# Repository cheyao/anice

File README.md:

# Icedev & Anice

*"FPGAs work like this. You don't tell them what to do, you tell them what to BE."*

An FPGA is a chip that can be configured on the hardware level. You can basically make your own CPU and GPU on it.

This project is composed of a PCB duo, that will be later joined together:

The first PCB called "icedev" is a ICE40 FPGA development board:
- 16MHz clock
- 64KiB eeprom
- 128MiB flash
- 1.2MiB of RAM
- dual usb-c
- multi voltage
It's equivalent is like the raspberry pico (orph pico)

The second, called "anice":
- 256MiB of ram
- 128MiB of flash
- HDMI port
- triple USB C with JTAG converter
- SDCard Reader
- dual 25MHz clock and 200MHz built-in clock
- multiple indicator lights
- only 4 layer PCB

View online demo on [kicanvas](https://kicanvas.org/?github=https%3A%2F%2Fgithub.com%2Fcheyao%2Fanice%2Ftree%2Fmain%2Fsrc%2F)!

The repo stucture is a bit messy because I wanted the two designs to appear together on kicanvas.

## Anice:

## Icedev:

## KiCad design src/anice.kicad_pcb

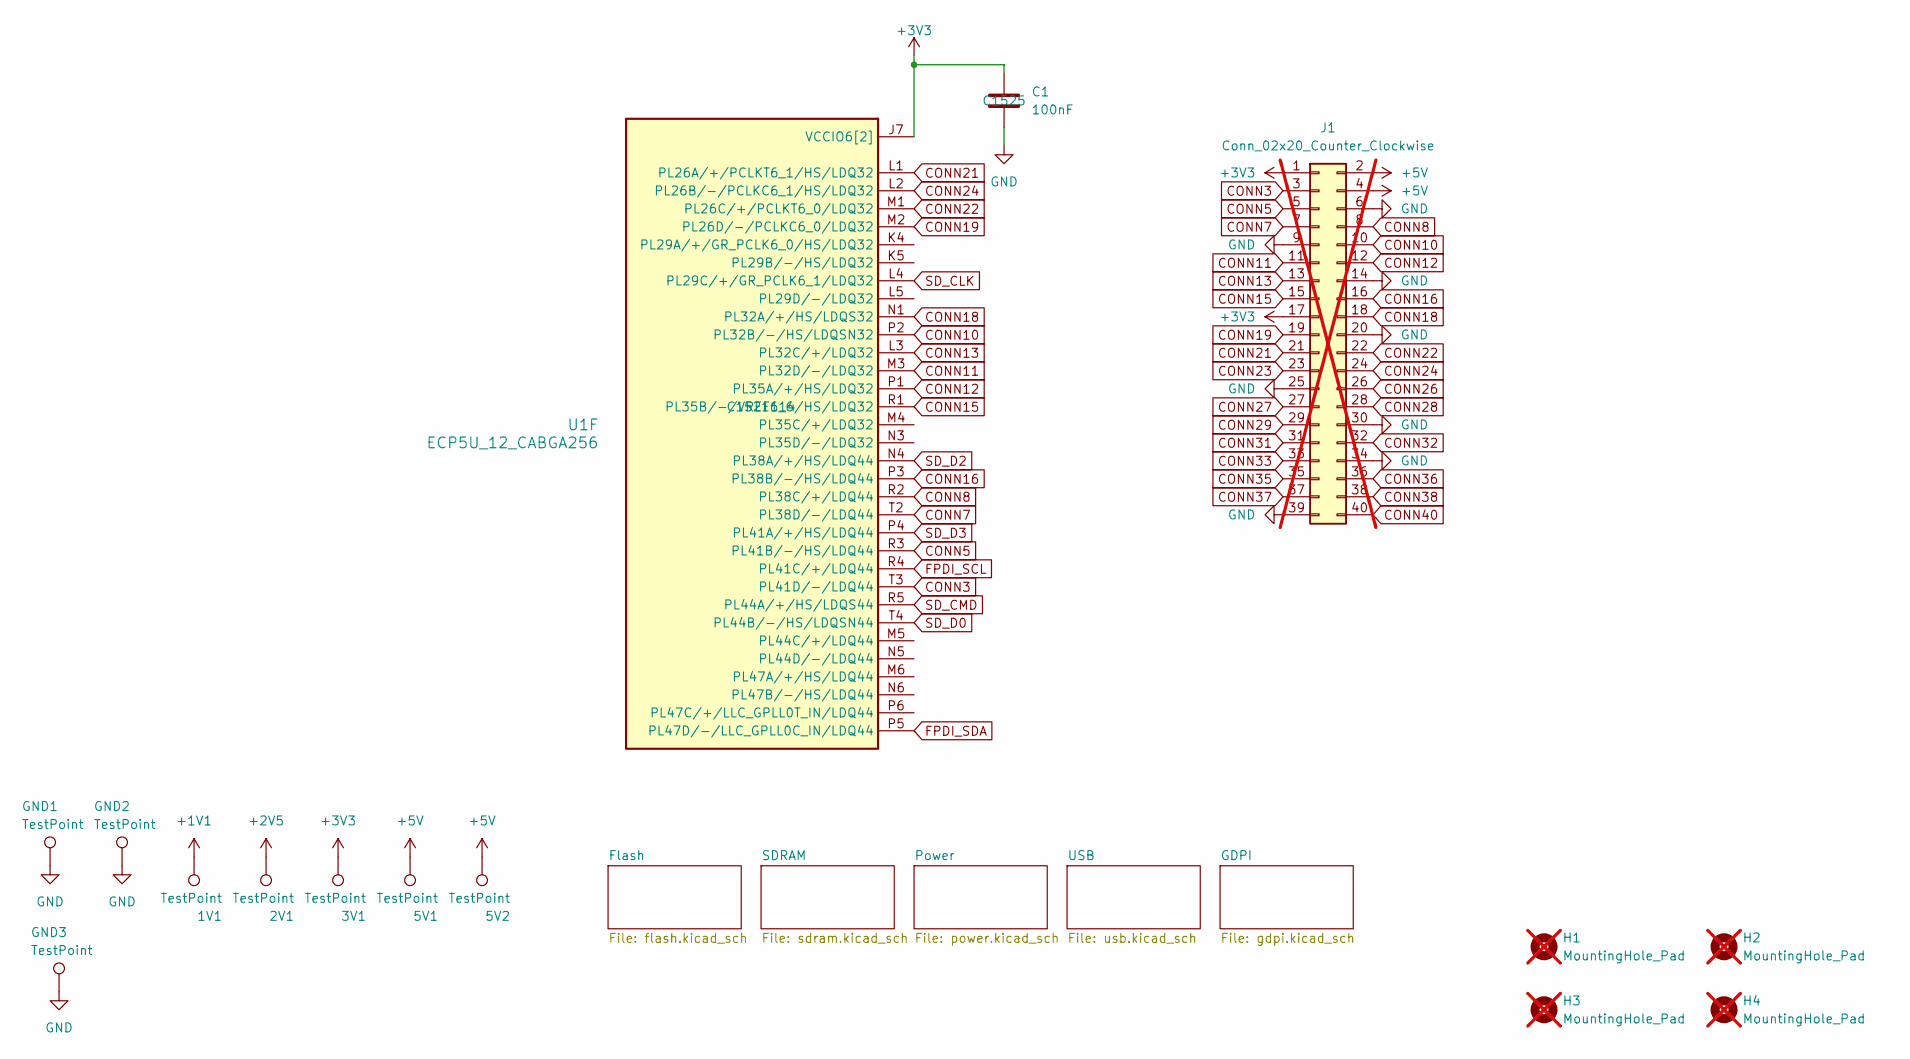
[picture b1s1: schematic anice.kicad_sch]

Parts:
1V1, 2V1, 3V1, 5V1, 5V2: TestPoint; TestPoint_Pad_D1.5mm
C1: 100nF; C_0402_1005Metric; JLCPCB Part # C1525
GND1, GND2, GND3: TestPoint; TestPoint_Pad_D1.5mm
H1, H2, H3, H4: MountingHole_Pad; MountingHole_2.5mm; not fitted
J1: Conn_02x20_Counter_Clockwise; PinHeader_2x20_P2.54mm_Vertical; not fitted
U1: ECP5U_12_CABGA256; BGA-256_14.0x14.0mm_Layout16x16_P0.8mm_Ball0.45mm_Pad0.32mm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; JLCPCB Part # C1521614

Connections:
+1V1: 1V1.1; also elsewhere on the board
+2V5: 2V1.1; also elsewhere on the board
+3V3: 3V1.1, C1.1, J1.1, J1.17, U1.J6 (VCCIO6[2]), U1.J7 (VCCIO6[2]); also elsewhere on the board
+5V: 5V1.1, 5V2.1, J1.2, J1.4; also elsewhere on the board
CONN3: J1.3, U1.T3 (PL41D/-/LDQ44)
CONN5: J1.5, U1.R3 (PL41B/-/HS/LDQ44)
CONN7: J1.7, U1.T2 (PL38D/-/LDQ44)
CONN8: J1.8, U1.R2 (PL38C/+/LDQ44)
CONN10: J1.10, U1.P2 (PL32B/-/HS/LDQSN32)
CONN11: J1.11, U1.M3 (PL32D/-/LDQ32)
CONN12: J1.12, U1.P1 (PL35A/+/HS/LDQ32)
CONN13: J1.13, U1.L3 (PL32C/+/LDQ32)
CONN15: J1.15, U1.R1 (PL35B/-/VREF1_6/HS/LDQ32)
CONN16: J1.16, U1.P3 (PL38B/-/HS/LDQ44)
CONN18: J1.18, U1.N1 (PL32A/+/HS/LDQS32)
CONN19: J1.19, U1.M2 (PL26D/-/PCLKC6_0/LDQ32)
CONN21: J1.21, U1.L1 (PL26A/+/PCLKT6_1/HS/LDQ32)
CONN22: J1.22, U1.M1 (PL26C/+/PCLKT6_0/LDQ32)
CONN23: J1.23; also elsewhere on the board
CONN24: J1.24, U1.L2 (PL26B/-/PCLKC6_1/HS/LDQ32)
CONN26: J1.26; also elsewhere on the board
CONN27: J1.27; also elsewhere on the board
CONN28: J1.28; also elsewhere on the board
CONN29: J1.29; also elsewhere on the board
CONN31: J1.31; also elsewhere on the board
CONN32: J1.32; also elsewhere on the board
CONN33: J1.33; also elsewhere on the board
CONN35: J1.35; also elsewhere on the board
CONN36: J1.36; also elsewhere on the board
CONN37: J1.37; also elsewhere on the board
CONN38: J1.38; also elsewhere on the board
CONN40: J1.40; also elsewhere on the board
FPDI_SCL: U1.R4 (PL41C/+/LDQ44); also elsewhere on the board
FPDI_SDA: U1.P5 (PL47D/-/LLC_GPLL0C_IN/LDQ44); also elsewhere on the board
GND: C1.2, GND1.1, GND2.1, GND3.1, J1.6, J1.9, J1.14, J1.20, J1.25, J1.30, J1.34, J1.39; also elsewhere on the board
SD_CLK: U1.L4 (PL29C/+/GR_PCLK6_1/LDQ32); also elsewhere on the board
SD_CMD: U1.R5 (PL44A/+/HS/LDQS44); also elsewhere on the board
SD_D0: U1.T4 (PL44B/-/HS/LDQSN44); also elsewhere on the board
SD_D2: U1.N4 (PL38A/+/HS/LDQ44); also elsewhere on the board
SD_D3: U1.P4 (PL41A/+/HS/LDQ44); also elsewhere on the board

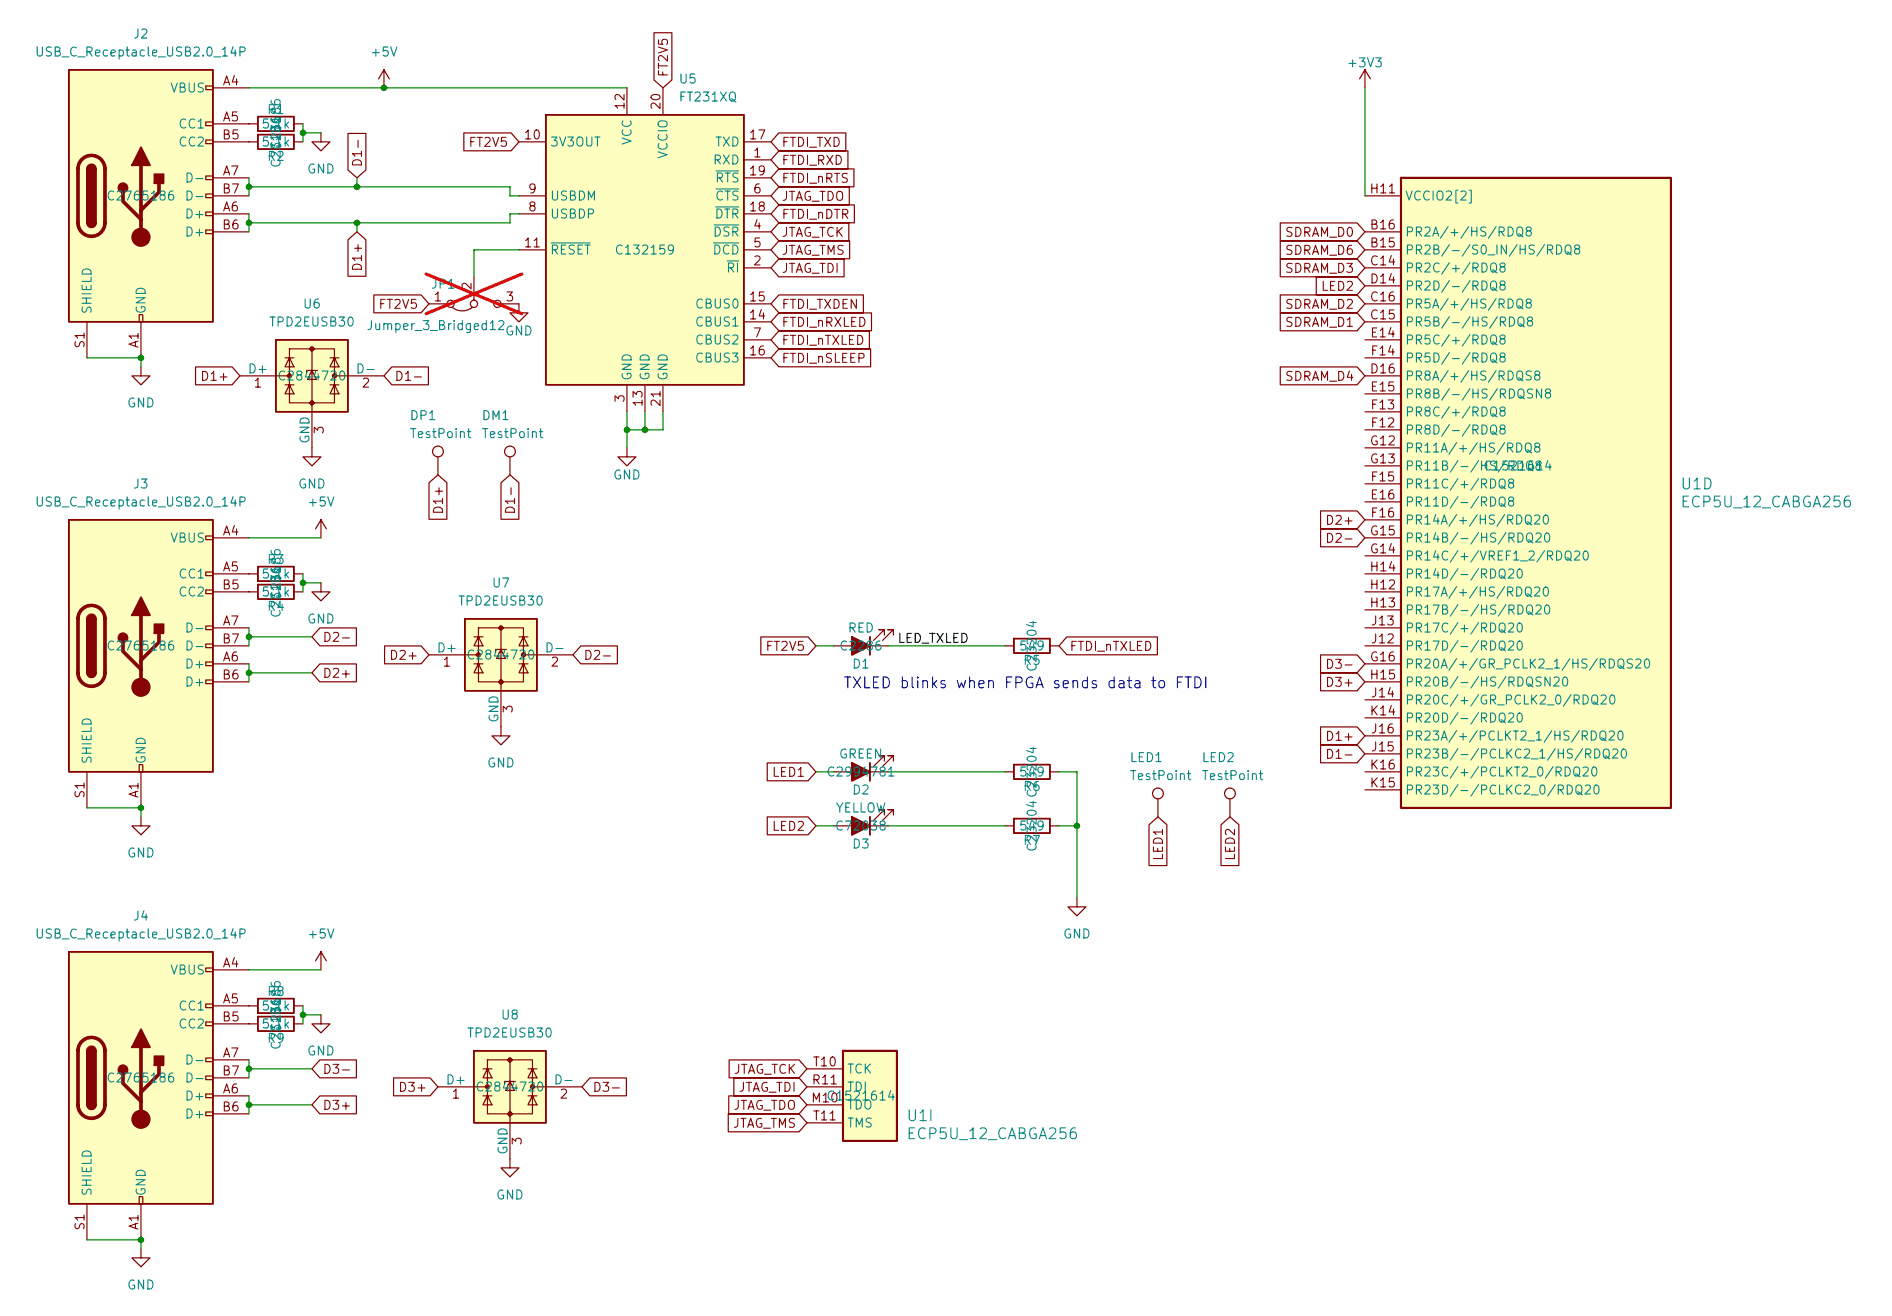
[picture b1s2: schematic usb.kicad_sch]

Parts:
D1: RED; LED_0603_1608Metric; JLCPCB Part # C2286
D2: GREEN; LED_0603_1608Metric; JLCPCB Part # C2994781
D3: YELLOW; LED_0603_1608Metric; JLCPCB Part # C72038
DM1: TestPoint; TestPoint_Pad_D1.5mm
DP1: TestPoint; TestPoint_Pad_D1.5mm
J2, J3, J4: USB_C_Receptacle_USB2.0_14P; USB_C_Receptacle_GCT_USB4105-xx-A_16P_TopMnt_Horizontal; JLCPCB Part # C2765186
JP1: Jumper_3_Bridged12; SolderJumper-3_P1.3mm_Bridged2Bar12_RoundedPad1.0x1.5mm; not fitted
LED1, LED2: TestPoint; TestPoint_Pad_D1.5mm
R1, R2, R3, R4, R8, R9: 5.1k; R_0603_1608Metric; JLCPCB Part # C23186
R5, R6, R7: 549; R_0603_1608Metric; JLCPCB Part # C23204
U1: ECP5U_12_CABGA256; BGA-256_14.0x14.0mm_Layout16x16_P0.8mm_Ball0.45mm_Pad0.32mm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; JLCPCB Part # C1521614
U5: FT231XQ; QFN-20-1EP_4x4mm_P0.5mm_EP2.5x2.5mm; JLCPCB Part # C132159
U6, U7, U8: TPD2EUSB30; Texas_DRT-3; JLCPCB Part # C2844720

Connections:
+3V3: U1.H11 (VCCIO2[2]), U1.J11 (VCCIO2[2]); also elsewhere on the board
+5V: J2.A4 (VBUS), J2.A9 (VBUS), J2.B4 (VBUS), J2.B9 (VBUS), J3.A4 (VBUS), J3.A9 (VBUS), J3.B4 (VBUS), J3.B9 (VBUS), J4.A4 (VBUS), J4.A9 (VBUS), J4.B4 (VBUS), J4.B9 (VBUS), U5.12 (VCC); also elsewhere on the board
/USB/LED_TXLED: D1.1 (K), R5.2
D1+: DP1.1, J2.A6 (D+), J2.B6 (D+), U1.J16 (PR23A/+/PCLKT2_1/HS/RDQ20), U5.8 (USBDP), U6.1 (D+)
D1-: DM1.1, J2.A7 (D-), J2.B7 (D-), U1.J15 (PR23B/-/PCLKC2_1/HS/RDQ20), U5.9 (USBDM), U6.2 (D-)
D2+: J3.A6 (D+), J3.B6 (D+), U1.F16 (PR14A/+/HS/RDQ20), U7.1 (D+)
D2-: J3.A7 (D-), J3.B7 (D-), U1.G15 (PR14B/-/HS/RDQ20), U7.2 (D-)
D3+: J4.A6 (D+), J4.B6 (D+), U1.H15 (PR20B/-/HS/RDQSN20), U8.1 (D+)
D3-: J4.A7 (D-), J4.B7 (D-), U1.G16 (PR20A/+/GR_PCLK2_1/HS/RDQS20), U8.2 (D-)
FT2V5: D1.2 (A), JP1.1 (A), U5.10 (3V3OUT), U5.20 (VCCIO)
FTDI_RXD: U5.1 (RXD)
FTDI_TXD: U5.17 (TXD)
FTDI_TXDEN: U5.15 (CBUS0)
FTDI_nDTR: U5.18 (~DTR)
FTDI_nRTS: U5.19 (~RTS)
FTDI_nRXLED: U5.14 (CBUS1)
FTDI_nSLEEP: U5.16 (CBUS3)
FTDI_nTXLED: R5.1, U5.7 (CBUS2)
GND: J2.A1 (GND), J2.A12 (GND), J2.B1 (GND), J2.B12 (GND), J2.S1 (SHIELD), J3.A1 (GND), J3.A12 (GND), J3.B1 (GND), J3.B12 (GND), J3.S1 (SHIELD), J4.A1 (GND), J4.A12 (GND), J4.B1 (GND), J4.B12 (GND), J4.S1 (SHIELD), JP1.3 (B), R1.1, R2.1, R3.1, R4.1, R6.1, R7.1, R8.1, R9.1, U5.3 (GND), U5.13 (GND), U5.21 (GND), U6.3 (GND), U7.3 (GND), U8.3 (GND); also elsewhere on the board
JTAG_TCK: U1.T10 (TCK), U5.4 (~DSR)
JTAG_TDI: U1.R11 (TDI), U5.2 (~RI)
JTAG_TDO: U1.M10 (TDO), U5.6 (~CTS)
JTAG_TMS: U1.T11 (TMS), U5.5 (~DCD)
LED1: D2.2 (A), LED1.1; also elsewhere on the board
LED2: D3.2 (A), LED2.1, U1.D14 (PR2D/-/RDQ8)
unnamed: D2.1 (K), R6.2
unnamed: D3.1 (K), R7.2
unnamed: J2.A5 (CC1), R1.2
unnamed: J2.B5 (CC2), R2.2
unnamed: J3.A5 (CC1), R3.2
unnamed: J3.B5 (CC2), R4.2
unnamed: J4.A5 (CC1), R8.2
unnamed: J4.B5 (CC2), R9.2
unnamed: JP1.2 (C), U5.11 (~RESET)
SDRAM_D0: U1.B16 (PR2A/+/HS/RDQ8); also elsewhere on the board
SDRAM_D1: U1.C15 (PR5B/-/HS/RDQ8); also elsewhere on the board
SDRAM_D2: U1.C16 (PR5A/+/HS/RDQ8); also elsewhere on the board
SDRAM_D3: U1.C14 (PR2C/+/RDQ8); also elsewhere on the board
SDRAM_D4: U1.D16 (PR8A/+/HS/RDQS8); also elsewhere on the board
SDRAM_D6: U1.B15 (PR2B/-/S0_IN/HS/RDQ8); also elsewhere on the board

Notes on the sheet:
TXLED blinks when FPGA sends data to FTDI

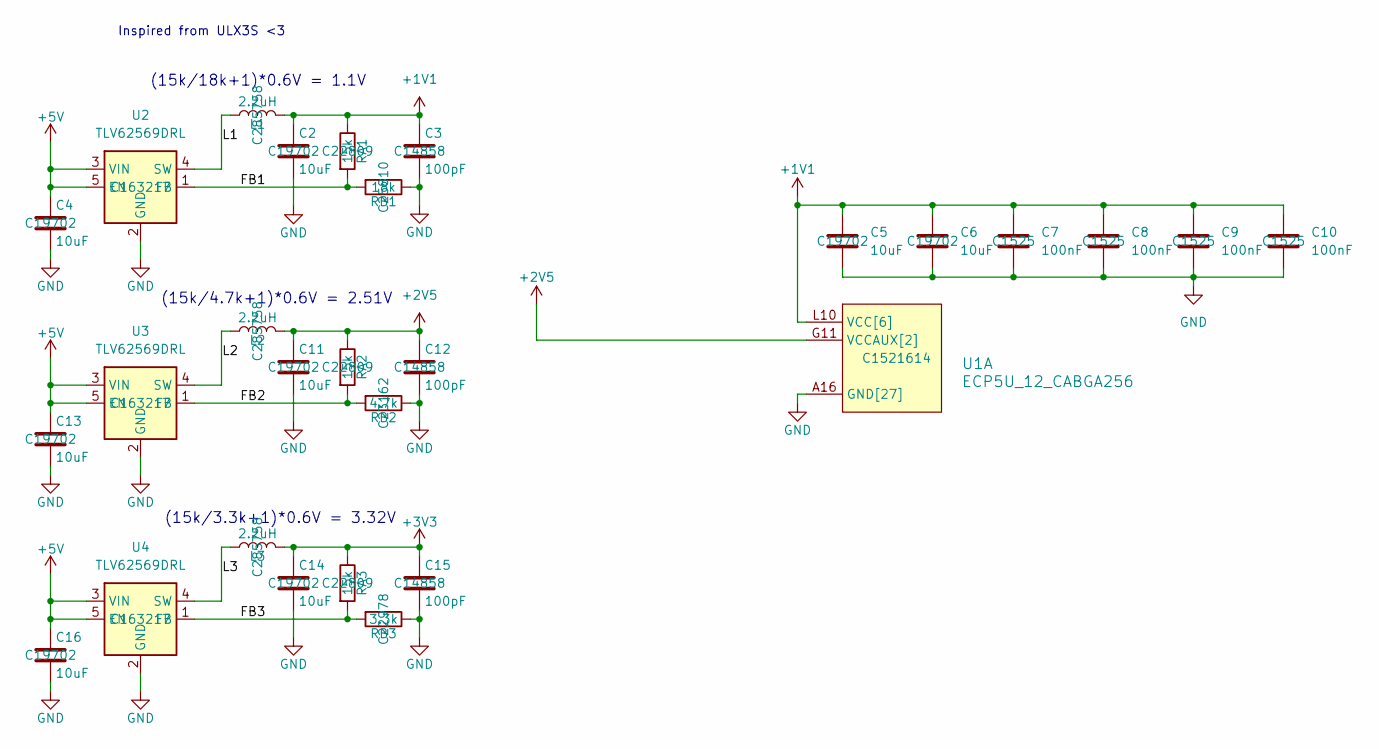
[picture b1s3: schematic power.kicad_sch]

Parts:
C2, C4, C5, C6, C11, C13, C14, C16: 10uF; C_0603_1608Metric; JLCPCB Part # C19702
C3, C12, C15: 100pF; C_0603_1608Metric; JLCPCB Part # C14858
C7, C8, C9, C10: 100nF; C_0402_1005Metric; JLCPCB Part # C1525
L1, L2, L3: 2.2uH; L_1008_2520Metric; JLCPCB Part # C285758
RA1, RA2, RA3: 15k; R_0603_1608Metric; JLCPCB Part # C22809
RB1: 18k; R_0603_1608Metric; JLCPCB Part # C25810
RB2: 4.7k; R_0603_1608Metric; JLCPCB Part # C23162
RB3: 3.3k; R_0603_1608Metric; JLCPCB Part # C22978
U1: ECP5U_12_CABGA256; BGA-256_14.0x14.0mm_Layout16x16_P0.8mm_Ball0.45mm_Pad0.32mm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; JLCPCB Part # C1521614
U2, U3, U4: TLV62569DRL; SOT-563; JLCPCB Part # C163217

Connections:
+1V1: C2.1, C3.1, C5.1, C6.1, C7.1, C8.1, C9.1, C10.1, L1.2, RA1.1, U1.G6 (VCC[6]), U1.G7 (VCC[6]), U1.G9 (VCC[6]), U1.L8 (VCC[6]), U1.L9 (VCC[6]), U1.L10 (VCC[6]); also elsewhere on the board
+2V5: C11.1, C12.1, L2.2, RA2.1, U1.G11 (VCCAUX[2]), U1.L7 (VCCAUX[2]); also elsewhere on the board
+3V3: C14.1, C15.1, L3.2, RA3.1; also elsewhere on the board
+5V: C4.1, C13.1, C16.1, U2.3 (VIN), U2.5 (EN), U3.3 (VIN), U3.5 (EN), U4.3 (VIN), U4.5 (EN); also elsewhere on the board
/Power/FB1: RA1.2, RB1.2, U2.1 (FB)
/Power/FB2: RA2.2, RB2.2, U3.1 (FB)
/Power/FB3: RA3.2, RB3.2, U4.1 (FB)
/Power/L1: L1.1, U2.4 (SW)
/Power/L2: L2.1, U3.4 (SW)
/Power/L3: L3.1, U4.4 (SW)
GND: C2.2, C3.2, C4.2, C5.2, C6.2, C7.2, C8.2, C9.2, C10.2, C11.2, C12.2, C13.2, C14.2, C15.2, C16.2, RB1.1, RB2.1, RB3.1, U1.A1 (GND[27]), U1.A16 (GND[27]), U1.D2 (GND[27]), U1.D15 (GND[27]), U1.F8 (GND[27]), U1.F9 (GND[27]), U1.G8 (GND[27]), U1.G10 (GND[27]), U1.H1 (GND[27]), U1.H8 (GND[27]), U1.H9 (GND[27]), U1.H10 (GND[27]), U1.H16 (GND[27]), U1.J8 (GND[27]), U1.J9 (GND[27]), U1.J10 (GND[27]), U1.K6 (GND[27]), U1.K7 (GND[27]), U1.K8 (GND[27]), U1.K9 (GND[27]), U1.K10 (GND[27]), U1.N2 (GND[27]), U1.N15 (GND[27]), U1.T1 (GND[27]), U1.T5 (GND[27]), U1.T12 (GND[27]), U1.T16 (GND[27]), U2.2 (GND), U3.2 (GND), U4.2 (GND); also elsewhere on the board

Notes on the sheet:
(15k/18k+1)*0.6V = 1.1V
(15k/4.7k+1)*0.6V = 2.51V
(15k/3.3k+1)*0.6V = 3.32V
Inspired from ULX3S <3

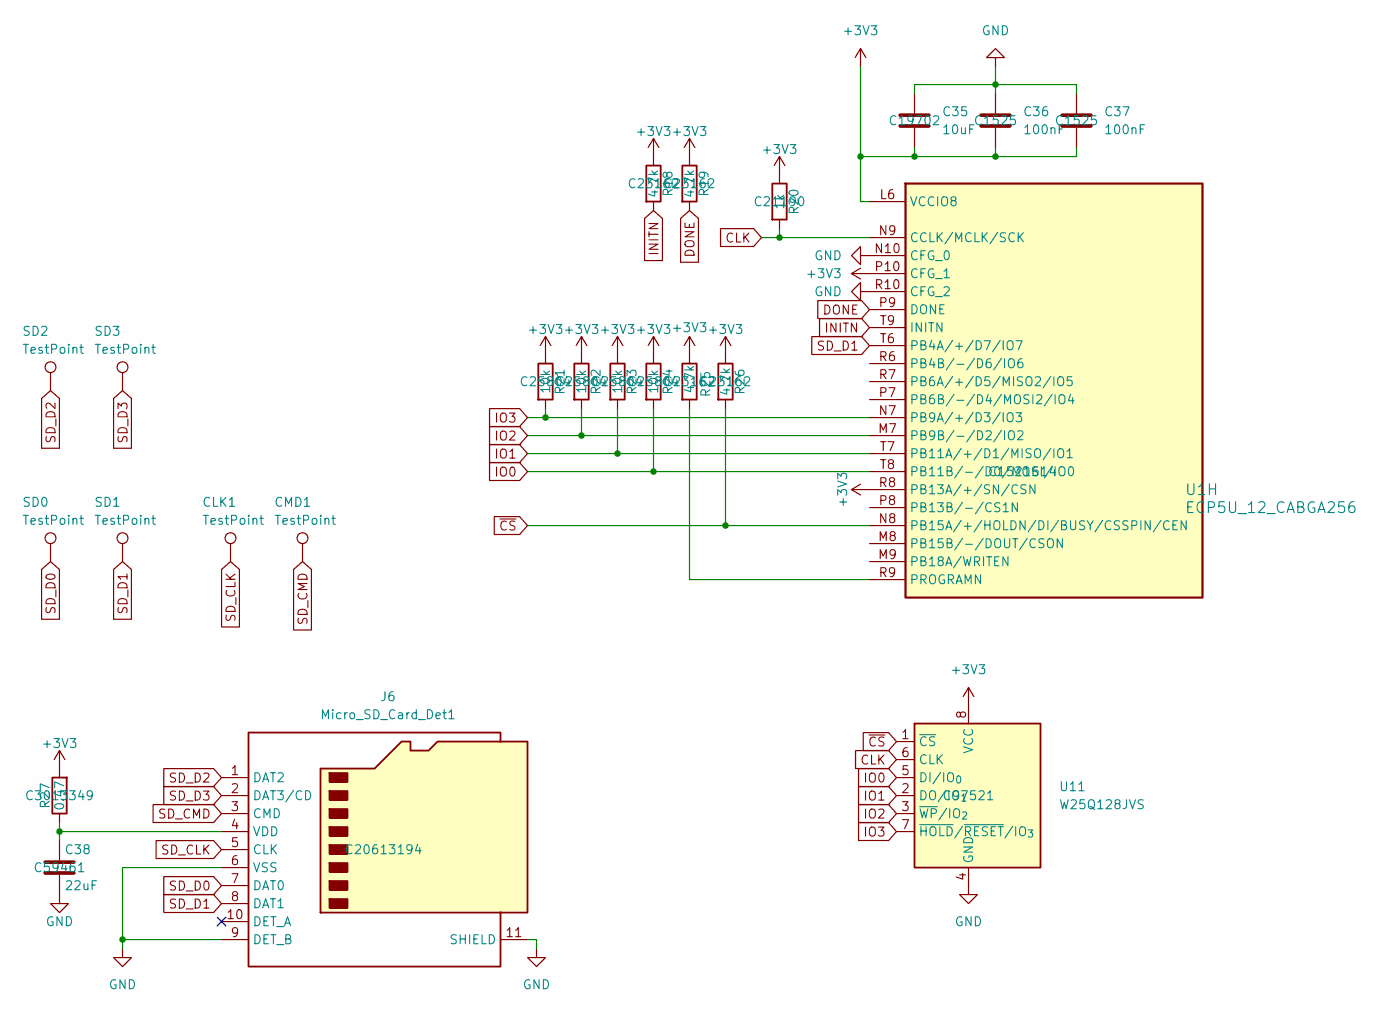
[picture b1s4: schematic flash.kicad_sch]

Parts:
C35: 10uF; C_0603_1608Metric; JLCPCB Part # C19702
C36, C37: 100nF; C_0402_1005Metric; JLCPCB Part # C1525
C38: 22uF; C_0603_1608Metric; JLCPCB Part # C59461
CLK1: TestPoint; TestPoint_Pad_D1.5mm
CMD1: TestPoint; TestPoint_Pad_D1.5mm
J6: Micro_SD_Card_Det1; SDCard molex; JLCPCB Part # C20613194
R18, R19, R25, R26: 4.7k; R_0603_1608Metric; JLCPCB Part # C23162
R20: 1k; R_0603_1608Metric; JLCPCB Part # C21190
R21, R22, R23, R24: 10k; R_0603_1608Metric; JLCPCB Part # C25804
R27: 0.47; R_0603_1608Metric; JLCPCB Part # C3013349
SD0, SD1, SD2, SD3: TestPoint; TestPoint_Pad_D1.5mm
U1: ECP5U_12_CABGA256; BGA-256_14.0x14.0mm_Layout16x16_P0.8mm_Ball0.45mm_Pad0.32mm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; JLCPCB Part # C1521614
U11: W25Q128JVS; SOIC-8_5.3x5.3mm_P1.27mm; JLCPCB Part # C97521

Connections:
+3V3: C35.2, C36.2, C37.2, R18.1, R19.1, R20.1, R21.1, R22.1, R23.1, R24.1, R25.1, R26.1, R27.2, U1.L6 (VCCIO8), U1.P10 (CFG_1), U1.R8 (PB13A/+/SN/CSN), U11.8 (VCC); also elsewhere on the board
CLK: R20.2, U1.N9 (CCLK/MCLK/SCK), U11.6 (CLK)
DONE: R19.2, U1.P9 (DONE)
GND: C35.1, C36.1, C37.1, C38.2, J6.6 (VSS), J6.9 (DET_B), J6.11 (SHIELD), U1.N10 (CFG_0), U1.R10 (CFG_2), U11.4 (GND); also elsewhere on the board
INITN: R18.2, U1.T9 (INITN)
IO0: R24.2, U1.T8 (PB11B/-/D0/MOSI/IO0), U11.5 (DI/IO_{0})
IO1: R23.2, U1.T7 (PB11A/+/D1/MISO/IO1), U11.2 (DO/IO_{1})
IO2: R22.2, U1.M7 (PB9B/-/D2/IO2), U11.3 (~WP/IO_{2})
IO3: R21.2, U1.N7 (PB9A/+/D3/IO3), U11.7 (~HOLD/~RESET/IO_{3})
unnamed: C38.1, J6.4 (VDD), R27.1
unnamed: R25.2, U1.R9 (PROGRAMN)
SD_CLK: CLK1.1, J6.5 (CLK); also elsewhere on the board
SD_CMD: CMD1.1, J6.3 (CMD); also elsewhere on the board
SD_D0: J6.7 (DAT0), SD0.1; also elsewhere on the board
SD_D1: J6.8 (DAT1), SD1.1, U1.T6 (PB4A/+/D7/IO7)
SD_D2: J6.1 (DAT2), SD2.1; also elsewhere on the board
SD_D3: J6.2 (DAT3/CD), SD3.1; also elsewhere on the board
~CS: R26.2, U1.N8 (PB15A/+/HOLDN/DI/BUSY/CSSPIN/CEN), U11.1 (~CS)

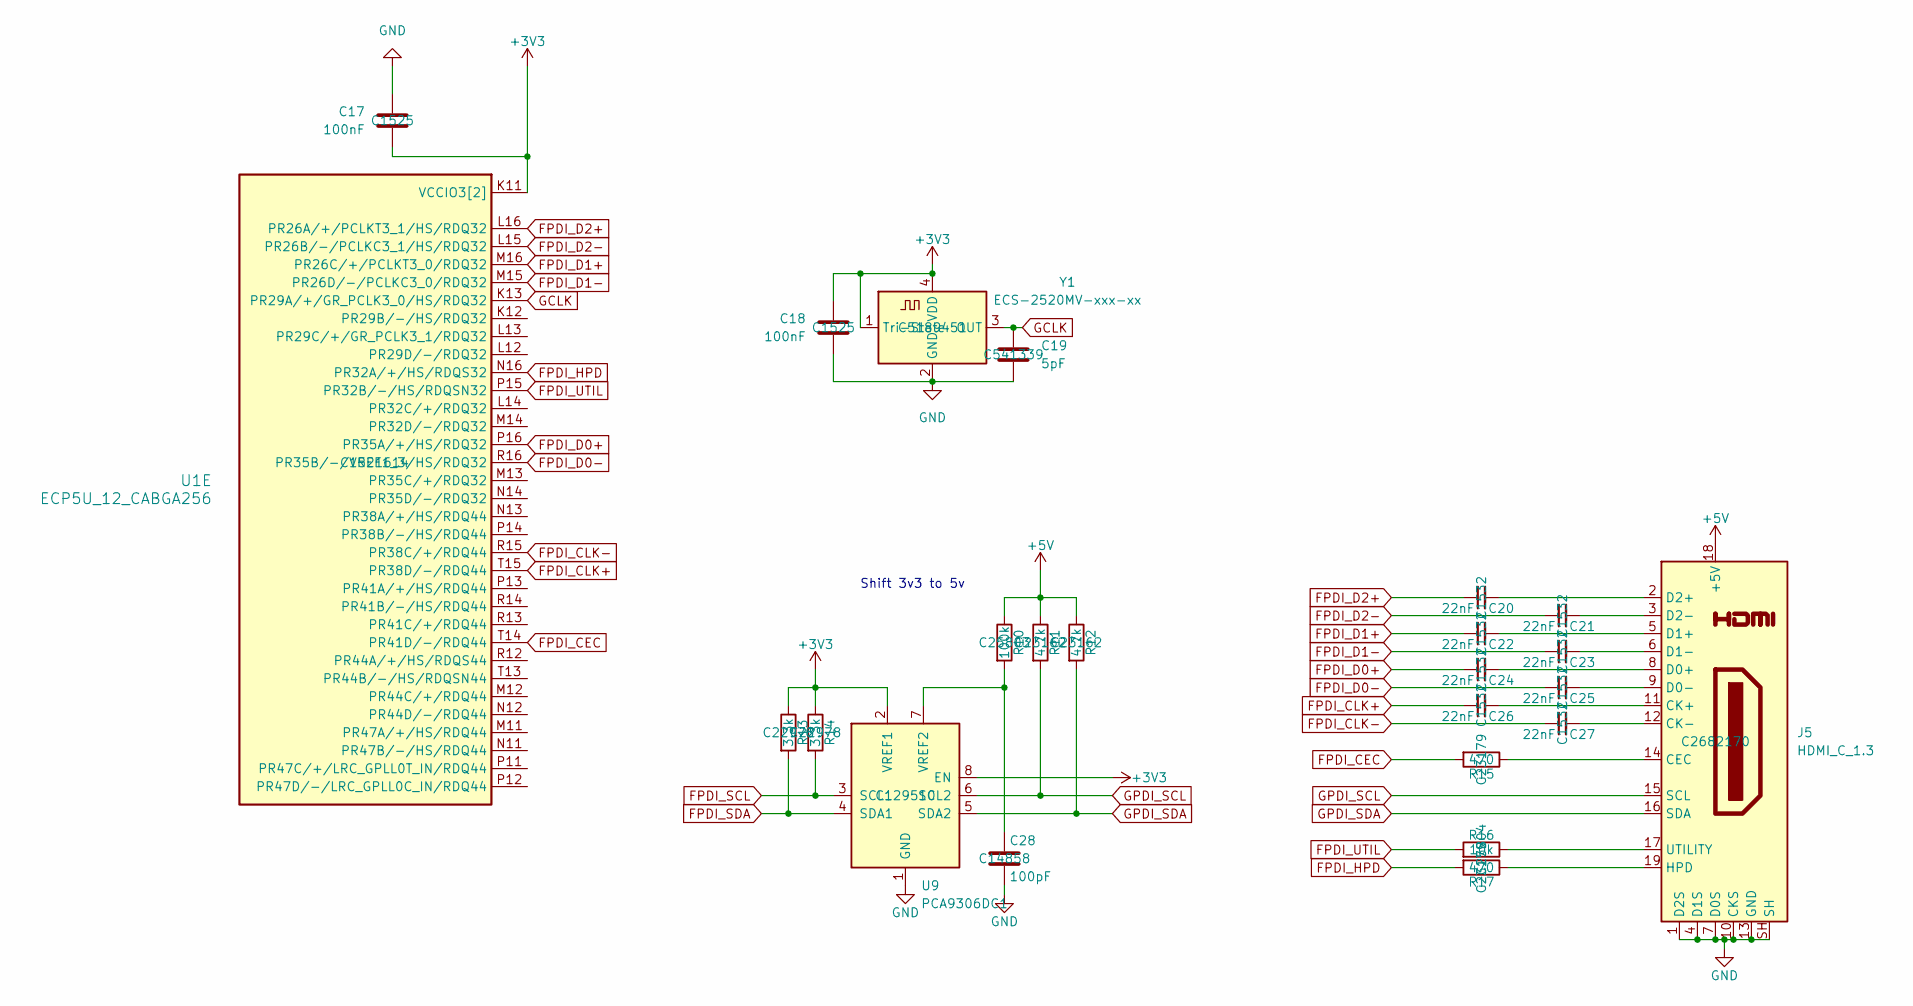
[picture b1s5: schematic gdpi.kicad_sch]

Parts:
C17, C18: 100nF; C_0402_1005Metric; JLCPCB Part # C1525
C19: 5pF; C_0402_1005Metric; JLCPCB Part # C541339
C20, C21, C22, C23, C24, C25, C26, C27: 22nF; C_0402_1005Metric; JLCPCB Part # C1532
C28: 100pF; C_0603_1608Metric; JLCPCB Part # C14858
J5: HDMI_C_1.3; XKB Connection A71-05H4-111N1; JLCPCB Part # C2682170
R10: 100k; R_0603_1608Metric; JLCPCB Part # C25803
R11, R12: 4.7k; R_0603_1608Metric; JLCPCB Part # C23162
R13, R14: 3.3k; R_0603_1608Metric; JLCPCB Part # C22978
R15, R17: 470; R_0603_1608Metric; JLCPCB Part # C23179
R16: 10k; R_0603_1608Metric; JLCPCB Part # C25804
U1: ECP5U_12_CABGA256; BGA-256_14.0x14.0mm_Layout16x16_P0.8mm_Ball0.45mm_Pad0.32mm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; JLCPCB Part # C1521614
U9: PCA9306DC1; VSSOP-8_2.3x2mm_P0.5mm; JLCPCB Part # C129510
Y1: ECS-2520MV-xxx-xx; Crystal_SMD_3225-4Pin_3.2x2.5mm; JLCPCB Part # C5189451

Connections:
+3V3: C17.2, C18.1, R13.1, R14.1, U1.K11 (VCCIO3[2]), U1.L11 (VCCIO3[2]), U9.2 (VREF1), U9.8 (EN), Y1.1 (Tri-State), Y1.4 (VDD); also elsewhere on the board
+5V: J5.18 (+5V), R10.1, R11.1, R12.1; also elsewhere on the board
FPDI_CEC: R15.2, U1.T14 (PR41D/-/RDQ44)
FPDI_CLK+: C26.1, U1.T15 (PR38D/-/RDQ44)
FPDI_CLK-: C27.1, U1.R15 (PR38C/+/RDQ44)
FPDI_D0+: C24.1, U1.P16 (PR35A/+/HS/RDQ32)
FPDI_D0-: C25.1, U1.R16 (PR35B/-/VREF1_3/HS/RDQ32)
FPDI_D1+: C22.1, U1.M16 (PR26C/+/PCLKT3_0/RDQ32)
FPDI_D1-: C23.1, U1.M15 (PR26D/-/PCLKC3_0/RDQ32)
FPDI_D2+: C20.1, U1.L16 (PR26A/+/PCLKT3_1/HS/RDQ32)
FPDI_D2-: C21.1, U1.L15 (PR26B/-/PCLKC3_1/HS/RDQ32)
FPDI_HPD: R17.2, U1.N16 (PR32A/+/HS/RDQS32)
FPDI_SCL: R14.2, U9.3 (SCL1); also elsewhere on the board
FPDI_SDA: R13.2, U9.4 (SDA1); also elsewhere on the board
FPDI_UTIL: R16.2, U1.P15 (PR32B/-/HS/RDQSN32)
GCLK: C19.1, U1.K13 (PR29A/+/GR_PCLK3_0/HS/RDQ32), Y1.3 (OUT)
GND: C17.1, C18.2, C19.2, C28.2, J5.1 (D2S), J5.4 (D1S), J5.7 (D0S), J5.10 (CKS), J5.13 (GND), J5.SH, U9.1 (GND), Y1.2 (GND); also elsewhere on the board
GPDI_SCL: J5.15 (SCL), R11.2, U9.6 (SCL2)
GPDI_SDA: J5.16 (SDA), R12.2, U9.5 (SDA2)
unnamed: J5.14 (CEC), R15.1
unnamed: C26.2, J5.11 (CK+)
unnamed: C27.2, J5.12 (CK-)
unnamed: C24.2, J5.8 (D0+)
unnamed: C25.2, J5.9 (D0-)
unnamed: C22.2, J5.5 (D1+)
unnamed: C23.2, J5.6 (D1-)
unnamed: C20.2, J5.2 (D2+)
unnamed: C21.2, J5.3 (D2-)
unnamed: J5.19 (HPD), R17.1
unnamed: J5.17 (UTILITY), R16.1
unnamed: C28.1, R10.2, U9.7 (VREF2)

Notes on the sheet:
Shift 3v3 to 5v

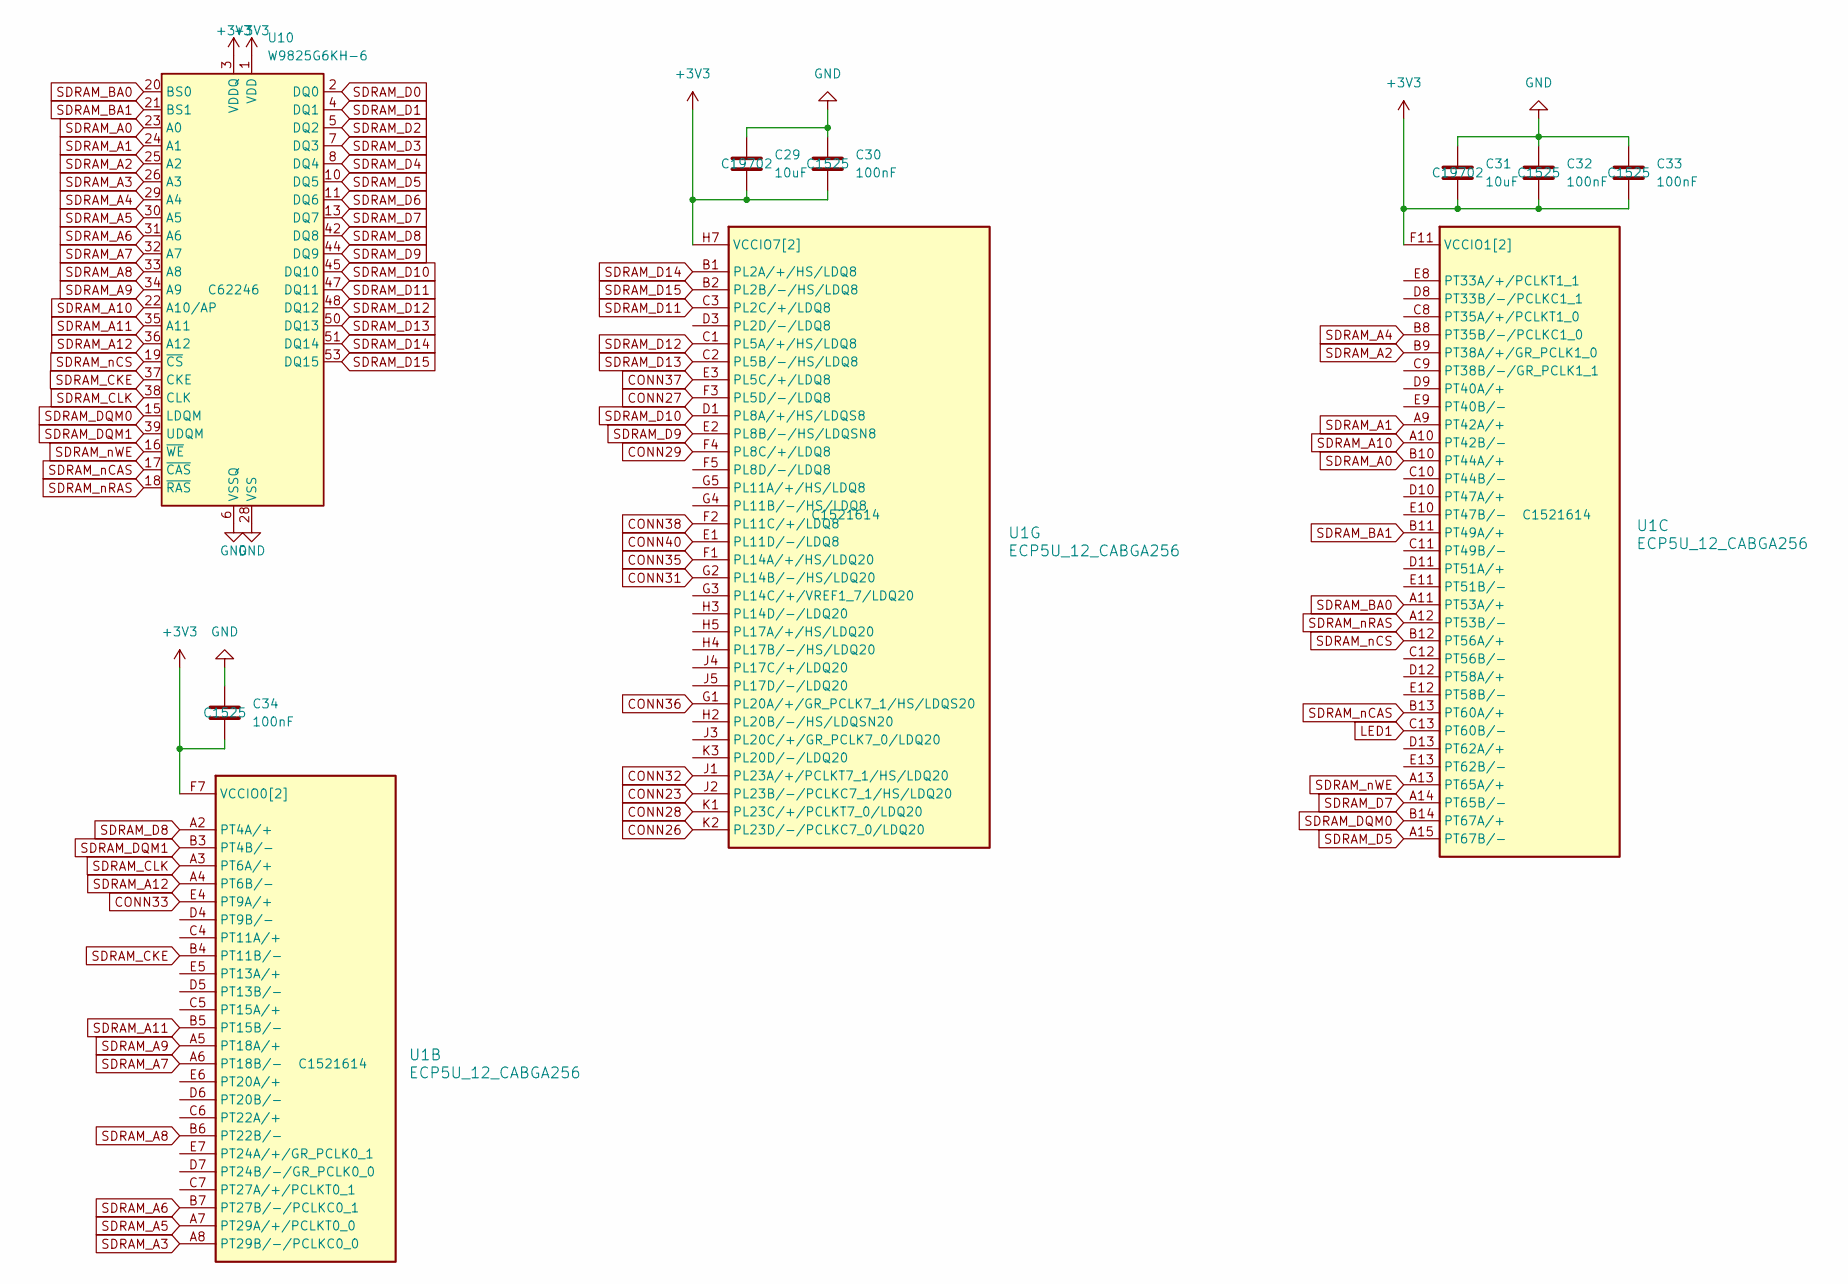
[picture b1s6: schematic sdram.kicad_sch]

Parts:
C29, C31: 10uF; C_0603_1608Metric; JLCPCB Part # C19702
C30, C32, C33, C34: 100nF; C_0402_1005Metric; JLCPCB Part # C1525
U1: ECP5U_12_CABGA256; BGA-256_14.0x14.0mm_Layout16x16_P0.8mm_Ball0.45mm_Pad0.32mm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; JLCPCB Part # C1521614
U10: W9825G6KH-6; TSOP-II-54_22.2x10.16mm_P0.8mm; JLCPCB Part # C62246

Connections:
+3V3: C29.2, C30.2, C31.2, C32.2, C33.2, C34.2, U1.F6 (VCCIO0[2]), U1.F7 (VCCIO0[2]), U1.F10 (VCCIO1[2]), U1.F11 (VCCIO1[2]), U1.H6 (VCCIO7[2]), U1.H7 (VCCIO7[2]), U10.1 (VDD), U10.3 (VDDQ), U10.9 (VDDQ), U10.14 (VDD), U10.27 (VDD), U10.43 (VDDQ), U10.49 (VDDQ); also elsewhere on the board
CONN23: U1.J2 (PL23B/-/PCLKC7_1/HS/LDQ20); also elsewhere on the board
CONN26: U1.K2 (PL23D/-/PCLKC7_0/LDQ20); also elsewhere on the board
CONN27: U1.F3 (PL5D/-/LDQ8); also elsewhere on the board
CONN28: U1.K1 (PL23C/+/PCLKT7_0/LDQ20); also elsewhere on the board
CONN29: U1.F4 (PL8C/+/LDQ8); also elsewhere on the board
CONN31: U1.G2 (PL14B/-/HS/LDQ20); also elsewhere on the board
CONN32: U1.J1 (PL23A/+/PCLKT7_1/HS/LDQ20); also elsewhere on the board
CONN33: U1.E4 (PT9A/+); also elsewhere on the board
CONN35: U1.F1 (PL14A/+/HS/LDQ20); also elsewhere on the board
CONN36: U1.G1 (PL20A/+/GR_PCLK7_1/HS/LDQS20); also elsewhere on the board
CONN37: U1.E3 (PL5C/+/LDQ8); also elsewhere on the board
CONN38: U1.F2 (PL11C/+/LDQ8); also elsewhere on the board
CONN40: U1.E1 (PL11D/-/LDQ8); also elsewhere on the board
GND: C29.1, C30.1, C31.1, C32.1, C33.1, C34.1, U10.6 (VSSQ), U10.12 (VSSQ), U10.28 (VSS), U10.41 (VSS), U10.46 (VSSQ), U10.52 (VSSQ), U10.54 (VSS); also elsewhere on the board
LED1: U1.C13 (PT60B/-); also elsewhere on the board
SDRAM_A0: U1.B10 (PT44A/+), U10.23 (A0)
SDRAM_A1: U1.A9 (PT42A/+), U10.24 (A1)
SDRAM_A2: U1.B9 (PT38A/+/GR_PCLK1_0), U10.25 (A2)
SDRAM_A3: U1.A8 (PT29B/-/PCLKC0_0), U10.26 (A3)
SDRAM_A4: U1.B8 (PT35B/-/PCLKC1_0), U10.29 (A4)
SDRAM_A5: U1.A7 (PT29A/+/PCLKT0_0), U10.30 (A5)
SDRAM_A6: U1.B7 (PT27B/-/PCLKC0_1), U10.31 (A6)
SDRAM_A7: U1.A6 (PT18B/-), U10.32 (A7)
SDRAM_A8: U1.B6 (PT22B/-), U10.33 (A8)
SDRAM_A9: U1.A5 (PT18A/+), U10.34 (A9)
SDRAM_A10: U1.A10 (PT42B/-), U10.22 (A10/AP)
SDRAM_A11: U1.B5 (PT15B/-), U10.35 (A11)
SDRAM_A12: U1.A4 (PT6B/-), U10.36 (A12)
SDRAM_BA0: U1.A11 (PT53A/+), U10.20 (BS0)
SDRAM_BA1: U1.B11 (PT49A/+), U10.21 (BS1)
SDRAM_CKE: U1.B4 (PT11B/-), U10.37 (CKE)
SDRAM_CLK: U1.A3 (PT6A/+), U10.38 (CLK)
SDRAM_D0: U10.2 (DQ0); also elsewhere on the board
SDRAM_D1: U10.4 (DQ1); also elsewhere on the board
SDRAM_D2: U10.5 (DQ2); also elsewhere on the board
SDRAM_D3: U10.7 (DQ3); also elsewhere on the board
SDRAM_D4: U10.8 (DQ4); also elsewhere on the board
SDRAM_D5: U1.A15 (PT67B/-), U10.10 (DQ5)
SDRAM_D6: U10.11 (DQ6); also elsewhere on the board
SDRAM_D7: U1.A14 (PT65B/-), U10.13 (DQ7)
SDRAM_D8: U1.A2 (PT4A/+), U10.42 (DQ8)
SDRAM_D9: U1.E2 (PL8B/-/HS/LDQSN8), U10.44 (DQ9)
SDRAM_D10: U1.D1 (PL8A/+/HS/LDQS8), U10.45 (DQ10)
SDRAM_D11: U1.C3 (PL2C/+/LDQ8), U10.47 (DQ11)
SDRAM_D12: U1.C1 (PL5A/+/HS/LDQ8), U10.48 (DQ12)
SDRAM_D13: U1.C2 (PL5B/-/HS/LDQ8), U10.50 (DQ13)
SDRAM_D14: U1.B1 (PL2A/+/HS/LDQ8), U10.51 (DQ14)
SDRAM_D15: U1.B2 (PL2B/-/HS/LDQ8), U10.53 (DQ15)
SDRAM_DQM0: U1.B14 (PT67A/+), U10.15 (LDQM)
SDRAM_DQM1: U1.B3 (PT4B/-), U10.39 (UDQM)
SDRAM_nCAS: U1.B13 (PT60A/+), U10.17 (~CAS)
SDRAM_nCS: U1.B12 (PT56A/+), U10.19 (~CS)
SDRAM_nRAS: U1.A12 (PT53B/-), U10.18 (~RAS)
SDRAM_nWE: U1.A13 (PT65A/+), U10.16 (~WE)

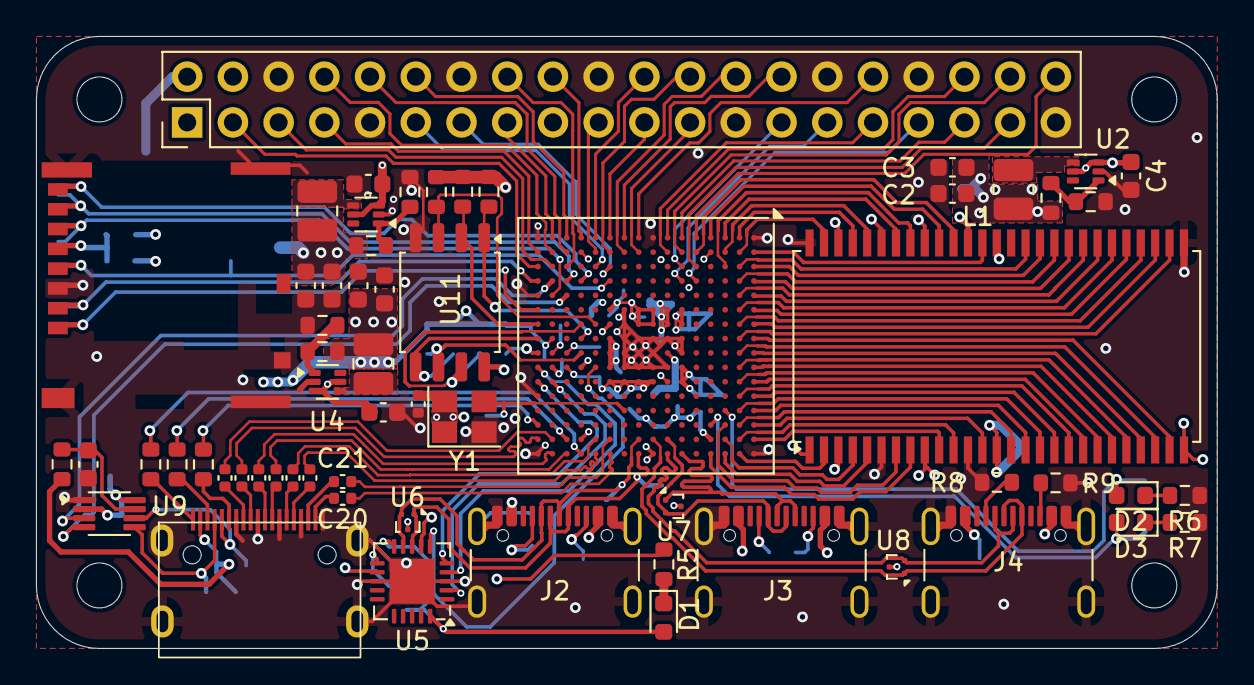
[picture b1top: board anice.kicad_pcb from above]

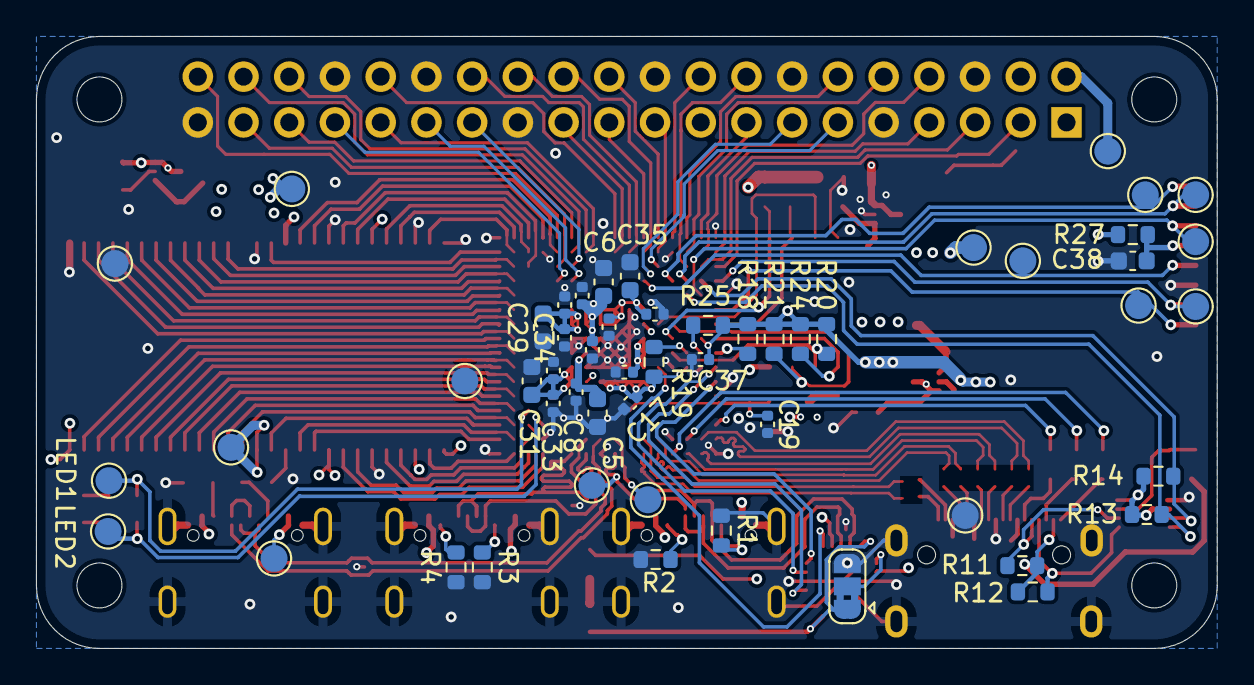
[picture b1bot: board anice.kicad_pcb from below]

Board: 4 copper layers, 65.6 x 34.0 mm, 118 parts (53 on the bottom side), 146 nets.
